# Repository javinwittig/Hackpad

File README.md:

# Hackpad

I made a custom 9-key macropad in a 3×3 layout, built with a Seeed Studio XIAO (SAMD21). Each switch has its own diode, wired as a 3×3 key matrix. It also features a small OLED display. 

## Features

- 9 mechanical keys in a 3×3 grid where each has its own diode
- Seeed Studio XIAO (SAMD21) as the controller 
- small OLED display
- Custom KiCad PCB
- Custom case modeled in Fusion 360, with cutouts for USB-C and the display header
- Firmware based on [KMK](https://github.com/KMKfw/kmk_firmware) (CircuitPython)

## Repository structure

| Folder | Contents |
| --- | --- |
| `Assets/` | Renders/photos used in this README (schematic, PCB, case) |
| `CAD/` | 3D assembly model (`Assembly1.0.step`) |
| `Firmware/` | `code.py` (KMK firmware source) and a compiled `.hex` build |
| `pcb/` | KiCad project (schematic + PCB layout, `.kicad_pro/.kicad_sch/.kicad_pcb`) |
| `Production/` | Manufacturing-ready files: case top/bottom (`.step`) and PCB `gerbers.zip` |

## Hardware

### Schematic

The controller is a **Seeed Studio XIAO (SAMD21)**. The 9 switches form a 3×3 diode matrix and a 4-pin header standard 2.54 mm pitch, GND–VCC–SCL–SDA) 

### PCB

Designed in **KiCad** (see `pcb/`). Manufacturing files (gerbers) are in `Production/gerbers.zip`.

### Case

I modeled the case in Fusion 360. The case features a cutout for the XIAO's USB-C port and an opening for the 4-pin display header. You'll find the STEP files for the top and bottom shells in Production/, and the full assembly is in CAD/Assembly1.0.step.
### Bill of Materials

| Part | Quantity |
| --- | --- |
| Seeed Studio XIAO | 1 |
| MX-style switches | 9 |
| 1N914 diodes | 9 |
| SSD1306 OLED display (128×32, I²C) | 1 |
| 4-pin header | 1 |
| M3 screws | 4 |

## Firmware
You can find the firmware in `Firmware/`or `Production/Firmware.py` and it is written for [KMK](https://github.com/KMKfw/kmk_firmware), a CircuitPython-based keyboard firmware. `code.py` is the source; a compiled `.hex` build is included as well.

What it does:
- Defines a 3×3 key matrix on `board.D0–D2` (columns) and `board.D7–D9` (rows), `COL2ROW` diode orientation
- Maps the 9 keys to the numpad keys `7 8 9 / 4 5 6 / 1 2 3`
- Drives an SSD1306 OLED over I²C to show status text ("Hackpad" / "9 Tasten")

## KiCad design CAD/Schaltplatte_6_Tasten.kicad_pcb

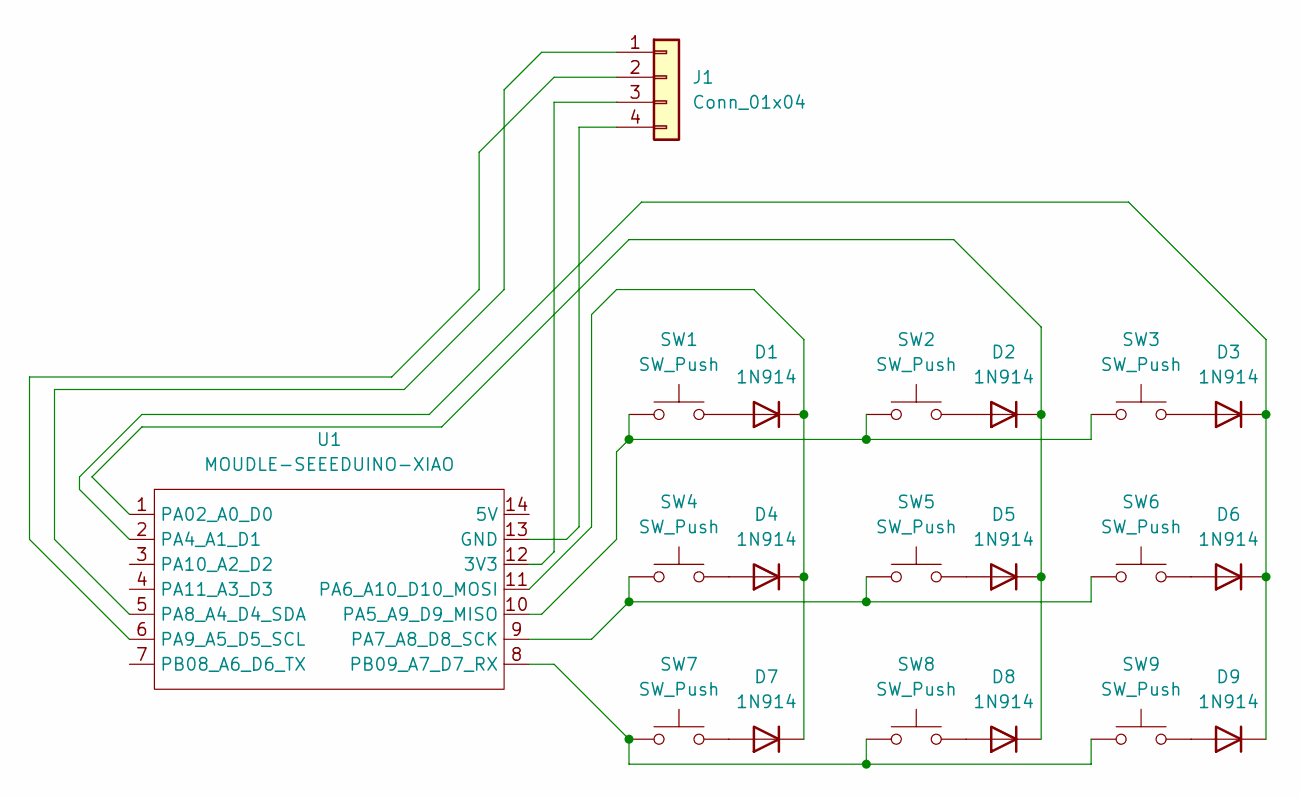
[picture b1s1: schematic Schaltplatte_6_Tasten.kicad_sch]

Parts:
D1, D2, D3, D4, D5, D6, D7, D8, D9: 1N914; D_DO-35_SOD27_P7.62mm_Horizontal
J1: Conn_01x04; PinHeader_1x04_P2.54mm_Vertical
SW1, SW2, SW3, SW4, SW5, SW6, SW7, SW8, SW9: SW_Push; SW_Cherry_MX_1.00u_PCB
U1: MOUDLE-SEEEDUINO-XIAO; XIAO-Generic-Hybrid-14P-2.54-21X17.8MM

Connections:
unnamed: D1.2 (A), SW1.2
unnamed: D1.1 (K), D4.1 (K), D7.1 (K), U1.11 (PA6_A10_D10_MOSI)
unnamed: D2.2 (A), SW2.2
unnamed: D2.1 (K), D5.1 (K), D8.1 (K), U1.1 (PA02_A0_D0)
unnamed: D3.2 (A), SW3.2
unnamed: D3.1 (K), D6.1 (K), D9.1 (K), U1.2 (PA4_A1_D1)
unnamed: D4.2 (A), SW4.2
unnamed: D5.2 (A), SW5.2
unnamed: D6.2 (A), SW6.2
unnamed: D7.2 (A), SW7.2
unnamed: D8.2 (A), SW8.2
unnamed: D9.2 (A), SW9.2
unnamed: J1.1, U1.5 (PA8_A4_D4_SDA)
unnamed: J1.2, U1.6 (PA9_A5_D5_SCL)
unnamed: J1.3, U1.12 (3V3)
unnamed: J1.4, U1.13 (GND)
unnamed: SW1.1, SW2.1, SW3.1, U1.10 (PA5_A9_D9_MISO)
unnamed: SW4.1, SW5.1, SW6.1, U1.9 (PA7_A8_D8_SCK)
unnamed: SW7.1, SW8.1, SW9.1, U1.8 (PB09_A7_D7_RX)

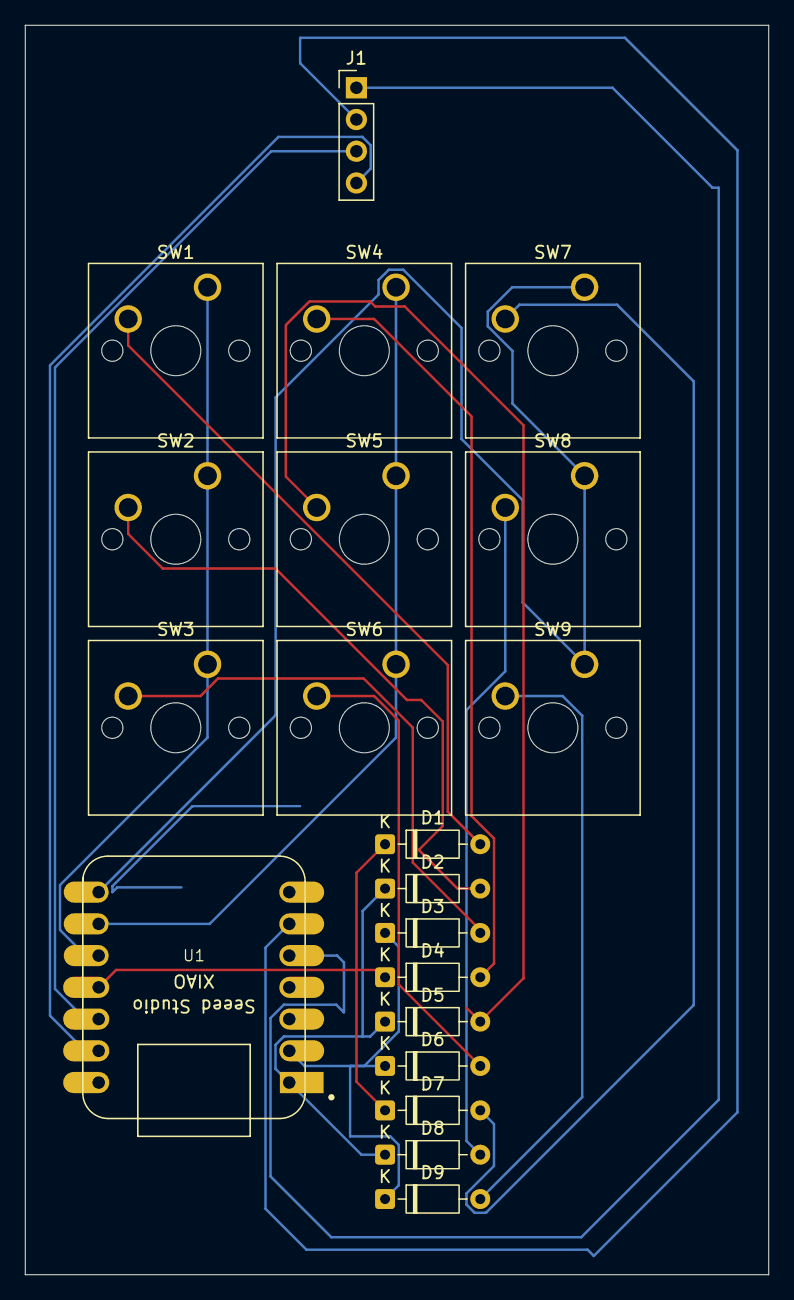
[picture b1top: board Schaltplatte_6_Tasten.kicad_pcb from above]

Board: 2 copper layers, 59.5 x 100.0 mm, 20 parts (0 on the bottom side), 19 nets.
